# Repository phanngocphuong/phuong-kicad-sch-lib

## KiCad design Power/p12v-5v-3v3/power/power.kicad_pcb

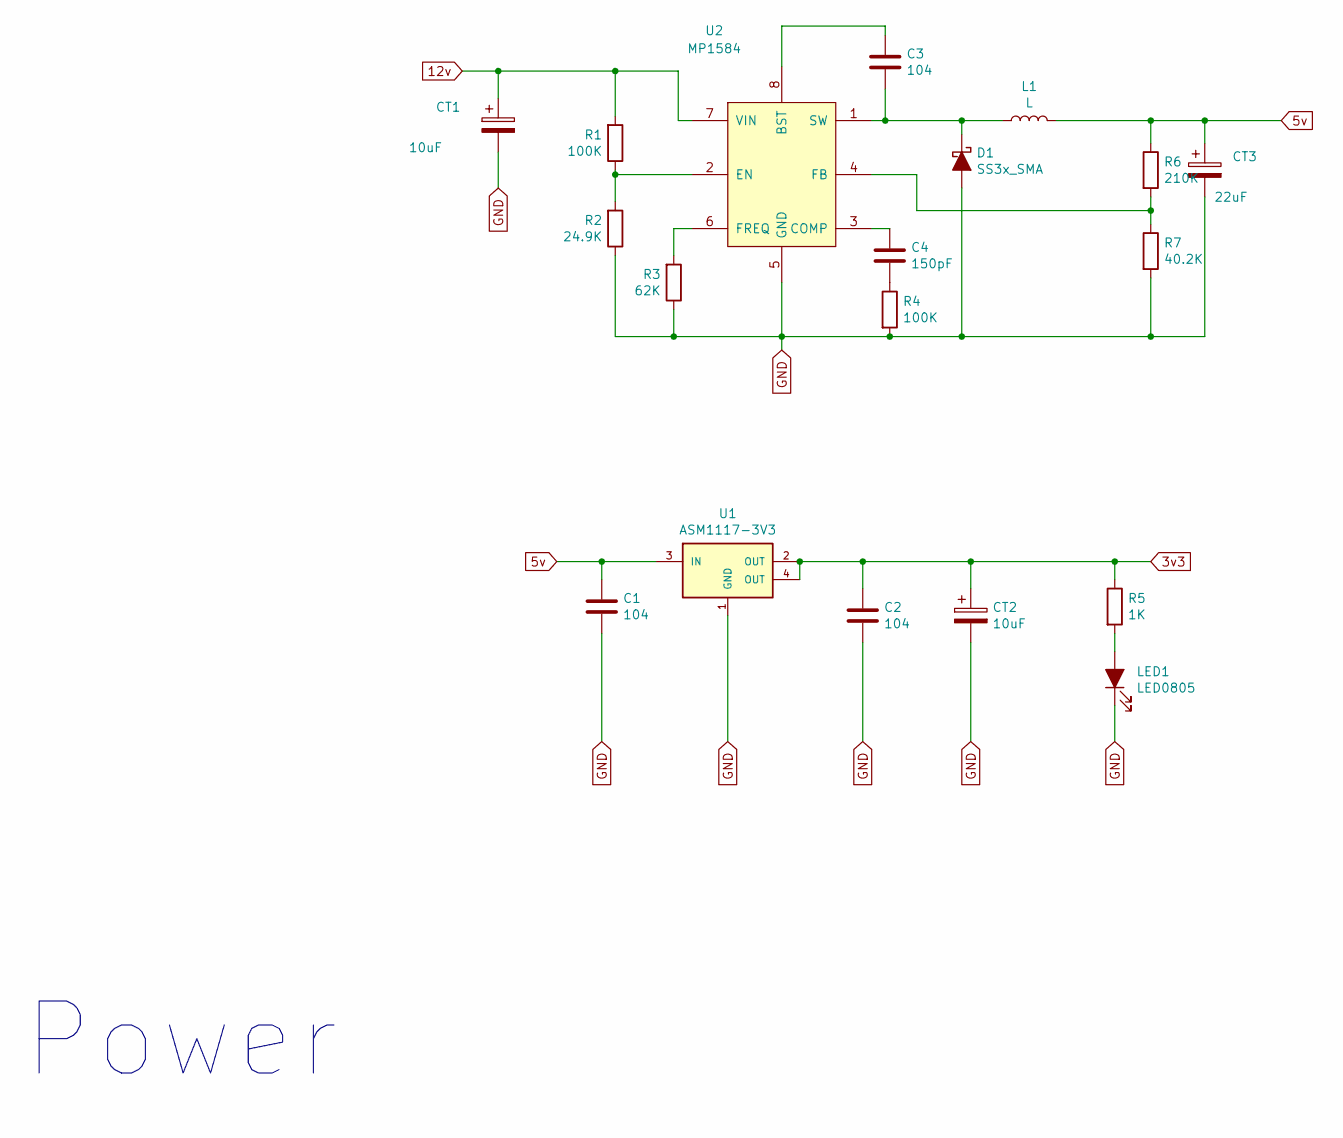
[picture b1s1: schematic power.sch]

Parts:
C1, C2, C3: 104; C_0805_HandSoldering
C4: 150pF; C_0805_HandSoldering
CT1, CT2: 10uF; CP_Tantalum_Case-B_EIA-3528-21_Reflow
CT3: 22uF; CP_Tantalum_Case-B_EIA-3528-21_Reflow
D1: SS3x_SMA; D_SMA
L1: L; L_5D28_HandSoldering
LED1: LED0805; LED_0805
R1, R4: 100K; R_0805_HandSoldering
R2: 24.9K; R_0805_HandSoldering
R3: 62K; R_0805_HandSoldering
R5: 1K; R_0805_HandSoldering
R6: 210K; R_0805_HandSoldering
R7: 40.2K; R_0603_HandSoldering
U1: ASM1117-3V3; SOT-223
U2: MP1584; SOIC-8-1EP_3.9x4.9mm_Pitch1.27mm

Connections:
3v3: C2.1, CT2.1, R5.1, U1.2 (OUT), U1.4 (OUT)
5v: C1.1, CT3.1, L1.2, R6.1, U1.3 (IN)
12v: CT1.1, R1.2, U2.7 (VIN)
GND: C1.2, C2.2, CT1.2, CT2.2, CT3.2, D1.2 (A), LED1.1 (K), R2.1, R3.1, R4.2, R7.2, U1.1 (GND), U2.5 (GND)
unnamed: C3.1, U2.8 (BST)
unnamed: C3.2, D1.1 (K), L1.1, U2.1 (SW)
unnamed: C4.1, U2.3 (COMP)
unnamed: C4.2, R4.1
unnamed: LED1.2 (A), R5.2
unnamed: R1.1, R2.2, U2.2 (EN)
unnamed: R3.2, U2.6 (FREQ)
unnamed: R6.2, R7.1, U2.4 (FB)

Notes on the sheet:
Power

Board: 2 copper layers, 19 parts (0 on the bottom side), 12 nets, no tracks yet.

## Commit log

2020-07-15 update power
